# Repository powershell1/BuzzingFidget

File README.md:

# BuzzingFidget

Controller board with 3 keys, 3 LEDs, a buzzer, and a potentiometer. When you press a key, the corresponding LED will light up. When you press all the keys together, the buzzer will sound, with the tone controlled by the potentiometer.

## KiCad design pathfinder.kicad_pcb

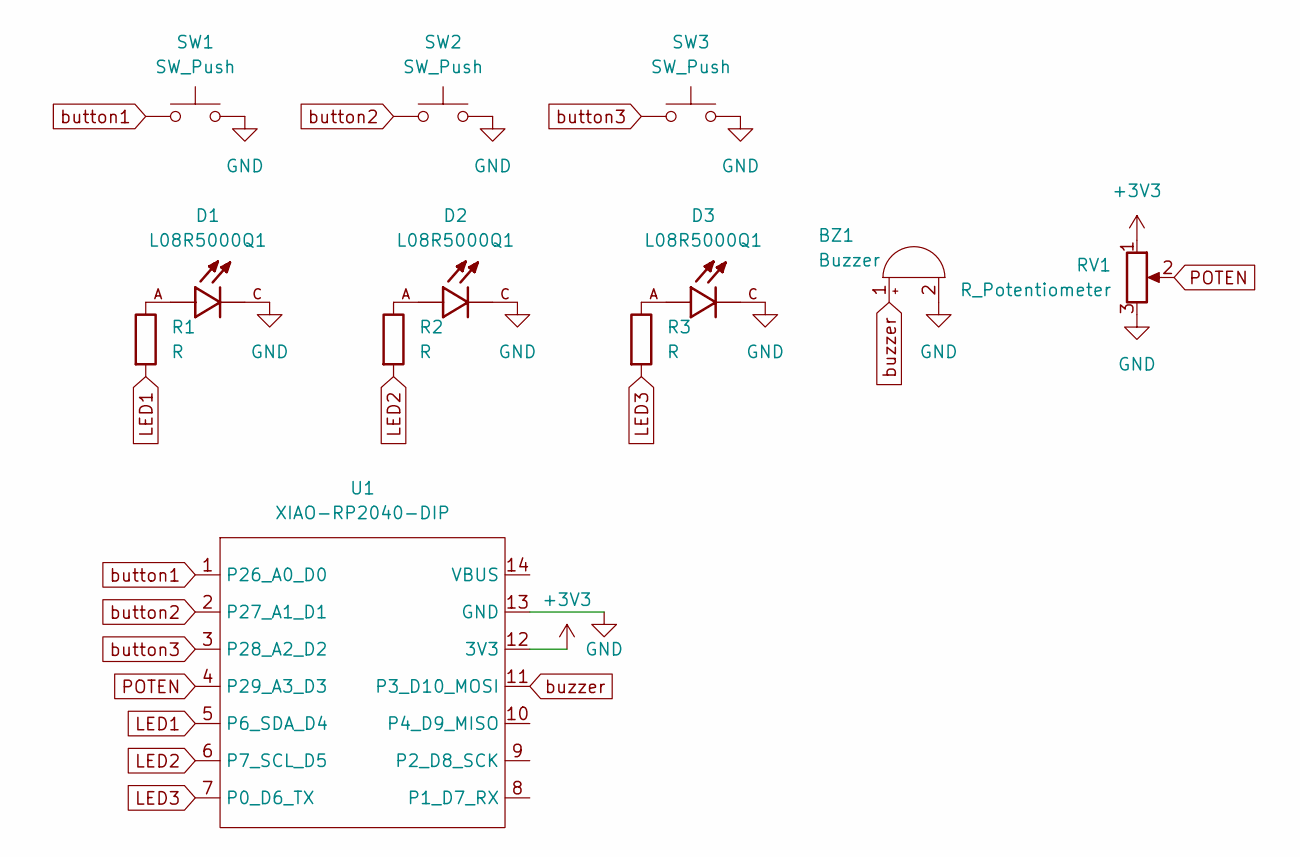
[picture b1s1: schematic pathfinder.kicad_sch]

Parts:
BZ1: Buzzer; Buzzer_12x9.5RM7.6
D1, D2, D3: L08R5000Q1; LEDRD254W57D500H1070; PARTREV NA
R1, R2, R3: R; R_Axial_DIN0204_L3.6mm_D1.6mm_P5.08mm_Horizontal
RV1: R_Potentiometer; Potentiometer_Vishay_T93YA_Vertical
SW1, SW2, SW3: SW_Push; SW_Cherry_MX_1.00u_PCB
U1: XIAO-RP2040-DIP

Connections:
+3V3: RV1.1, U1.12 (3V3)
GND: BZ1.2 (-), D1.C, D2.C, D3.C, RV1.3, SW1.2, SW2.2, SW3.2, U1.13 (GND)
LED1: R1.2, U1.5 (P6_SDA_D4)
LED2: R2.2, U1.6 (P7_SCL_D5)
LED3: R3.2, U1.7 (P0_D6_TX)
unnamed: D1.A, R1.1
unnamed: D2.A, R2.1
unnamed: D3.A, R3.1
POTEN: RV1.2, U1.4 (P29_A3_D3)
button1: SW1.1, U1.1 (P26_A0_D0)
button2: SW2.1, U1.2 (P27_A1_D1)
button3: SW3.1, U1.3 (P28_A2_D2)
buzzer: BZ1.1 (+), U1.11 (P3_D10_MOSI)

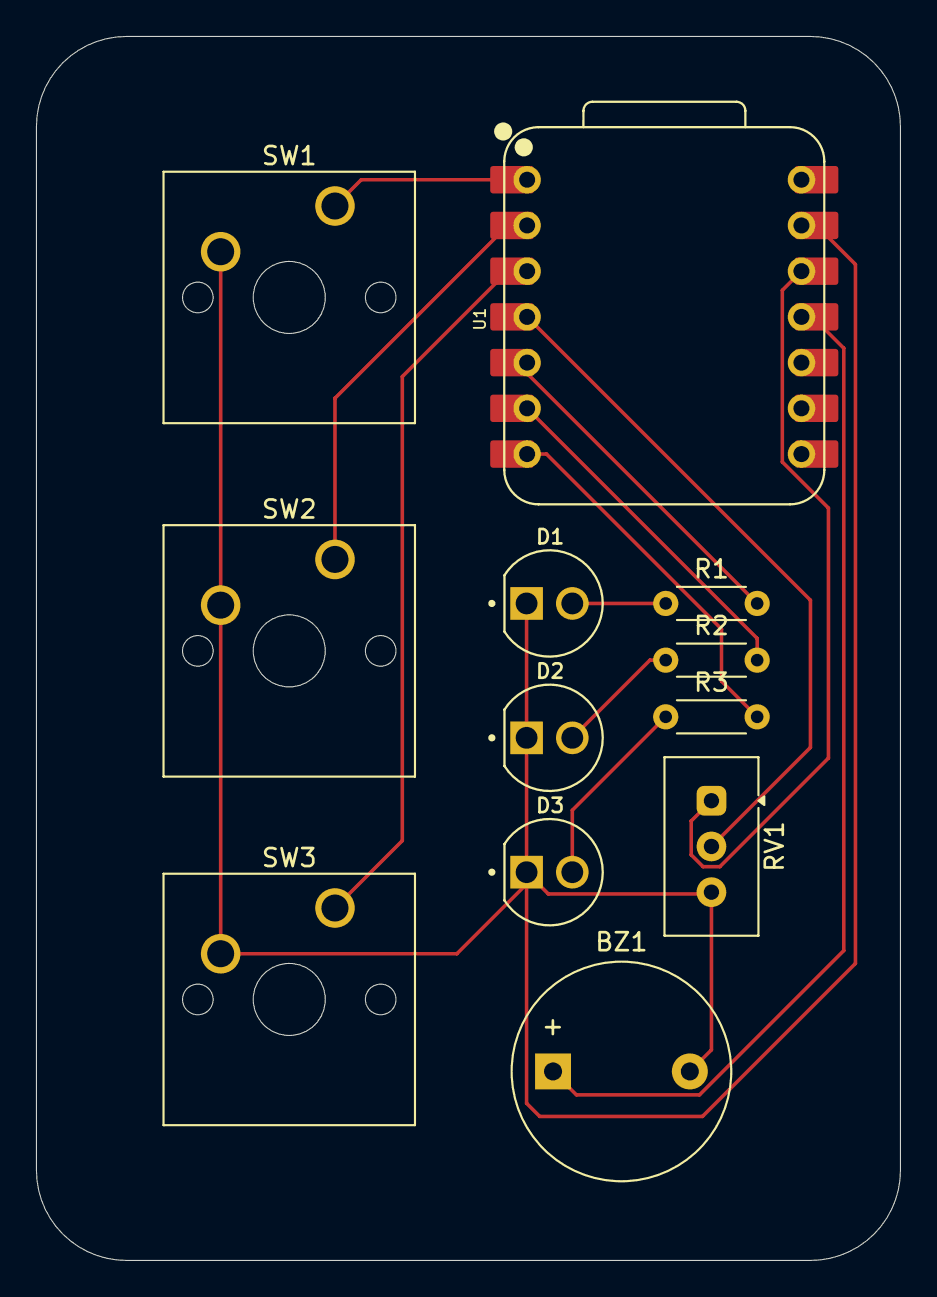
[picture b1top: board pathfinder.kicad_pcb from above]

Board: 2 copper layers, 48.0 x 68.0 mm, 12 parts (0 on the bottom side), 13 nets.

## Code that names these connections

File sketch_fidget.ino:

#define BTN1 D0
#define BTN2 D1
#define BTN3 D2
#define POTEN D3
#define LED1 D4
#define LED2 D5
#define LED3 D6
#define BUZZER D10

void setup() {
  pinMode(POTEN, INPUT);
  pinMode(BTN1, INPUT_PULLUP);
  pinMode(BTN2, INPUT_PULLUP);
  pinMode(BTN3, INPUT_PULLUP);
  
  pinMode(LED1, OUTPUT);
  pinMode(LED2, OUTPUT);
  pinMode(LED3, OUTPUT);
  pinMode(BUZZER, OUTPUT);
}

void loop() {
  bool btn1Read = digitalRead(BTN1);
  bool btn2Read = digitalRead(BTN2);
  bool btn3Read = digitalRead(BTN3);
  digitalWrite(LED1, btn1Read);
  digitalWrite(LED2, btn2Read);
  digitalWrite(LED3, btn3Read);

  if (btn1Read && btn2Read && btn3Read) {
    int potenRead = digitalRead(POTEN);
    double toneHz = map(potenRead, 0, 1023, 100, 3000);
    tone(BUZZER, (int)toneHz);
  } else {
    noTone(BUZZER);
  }
}
